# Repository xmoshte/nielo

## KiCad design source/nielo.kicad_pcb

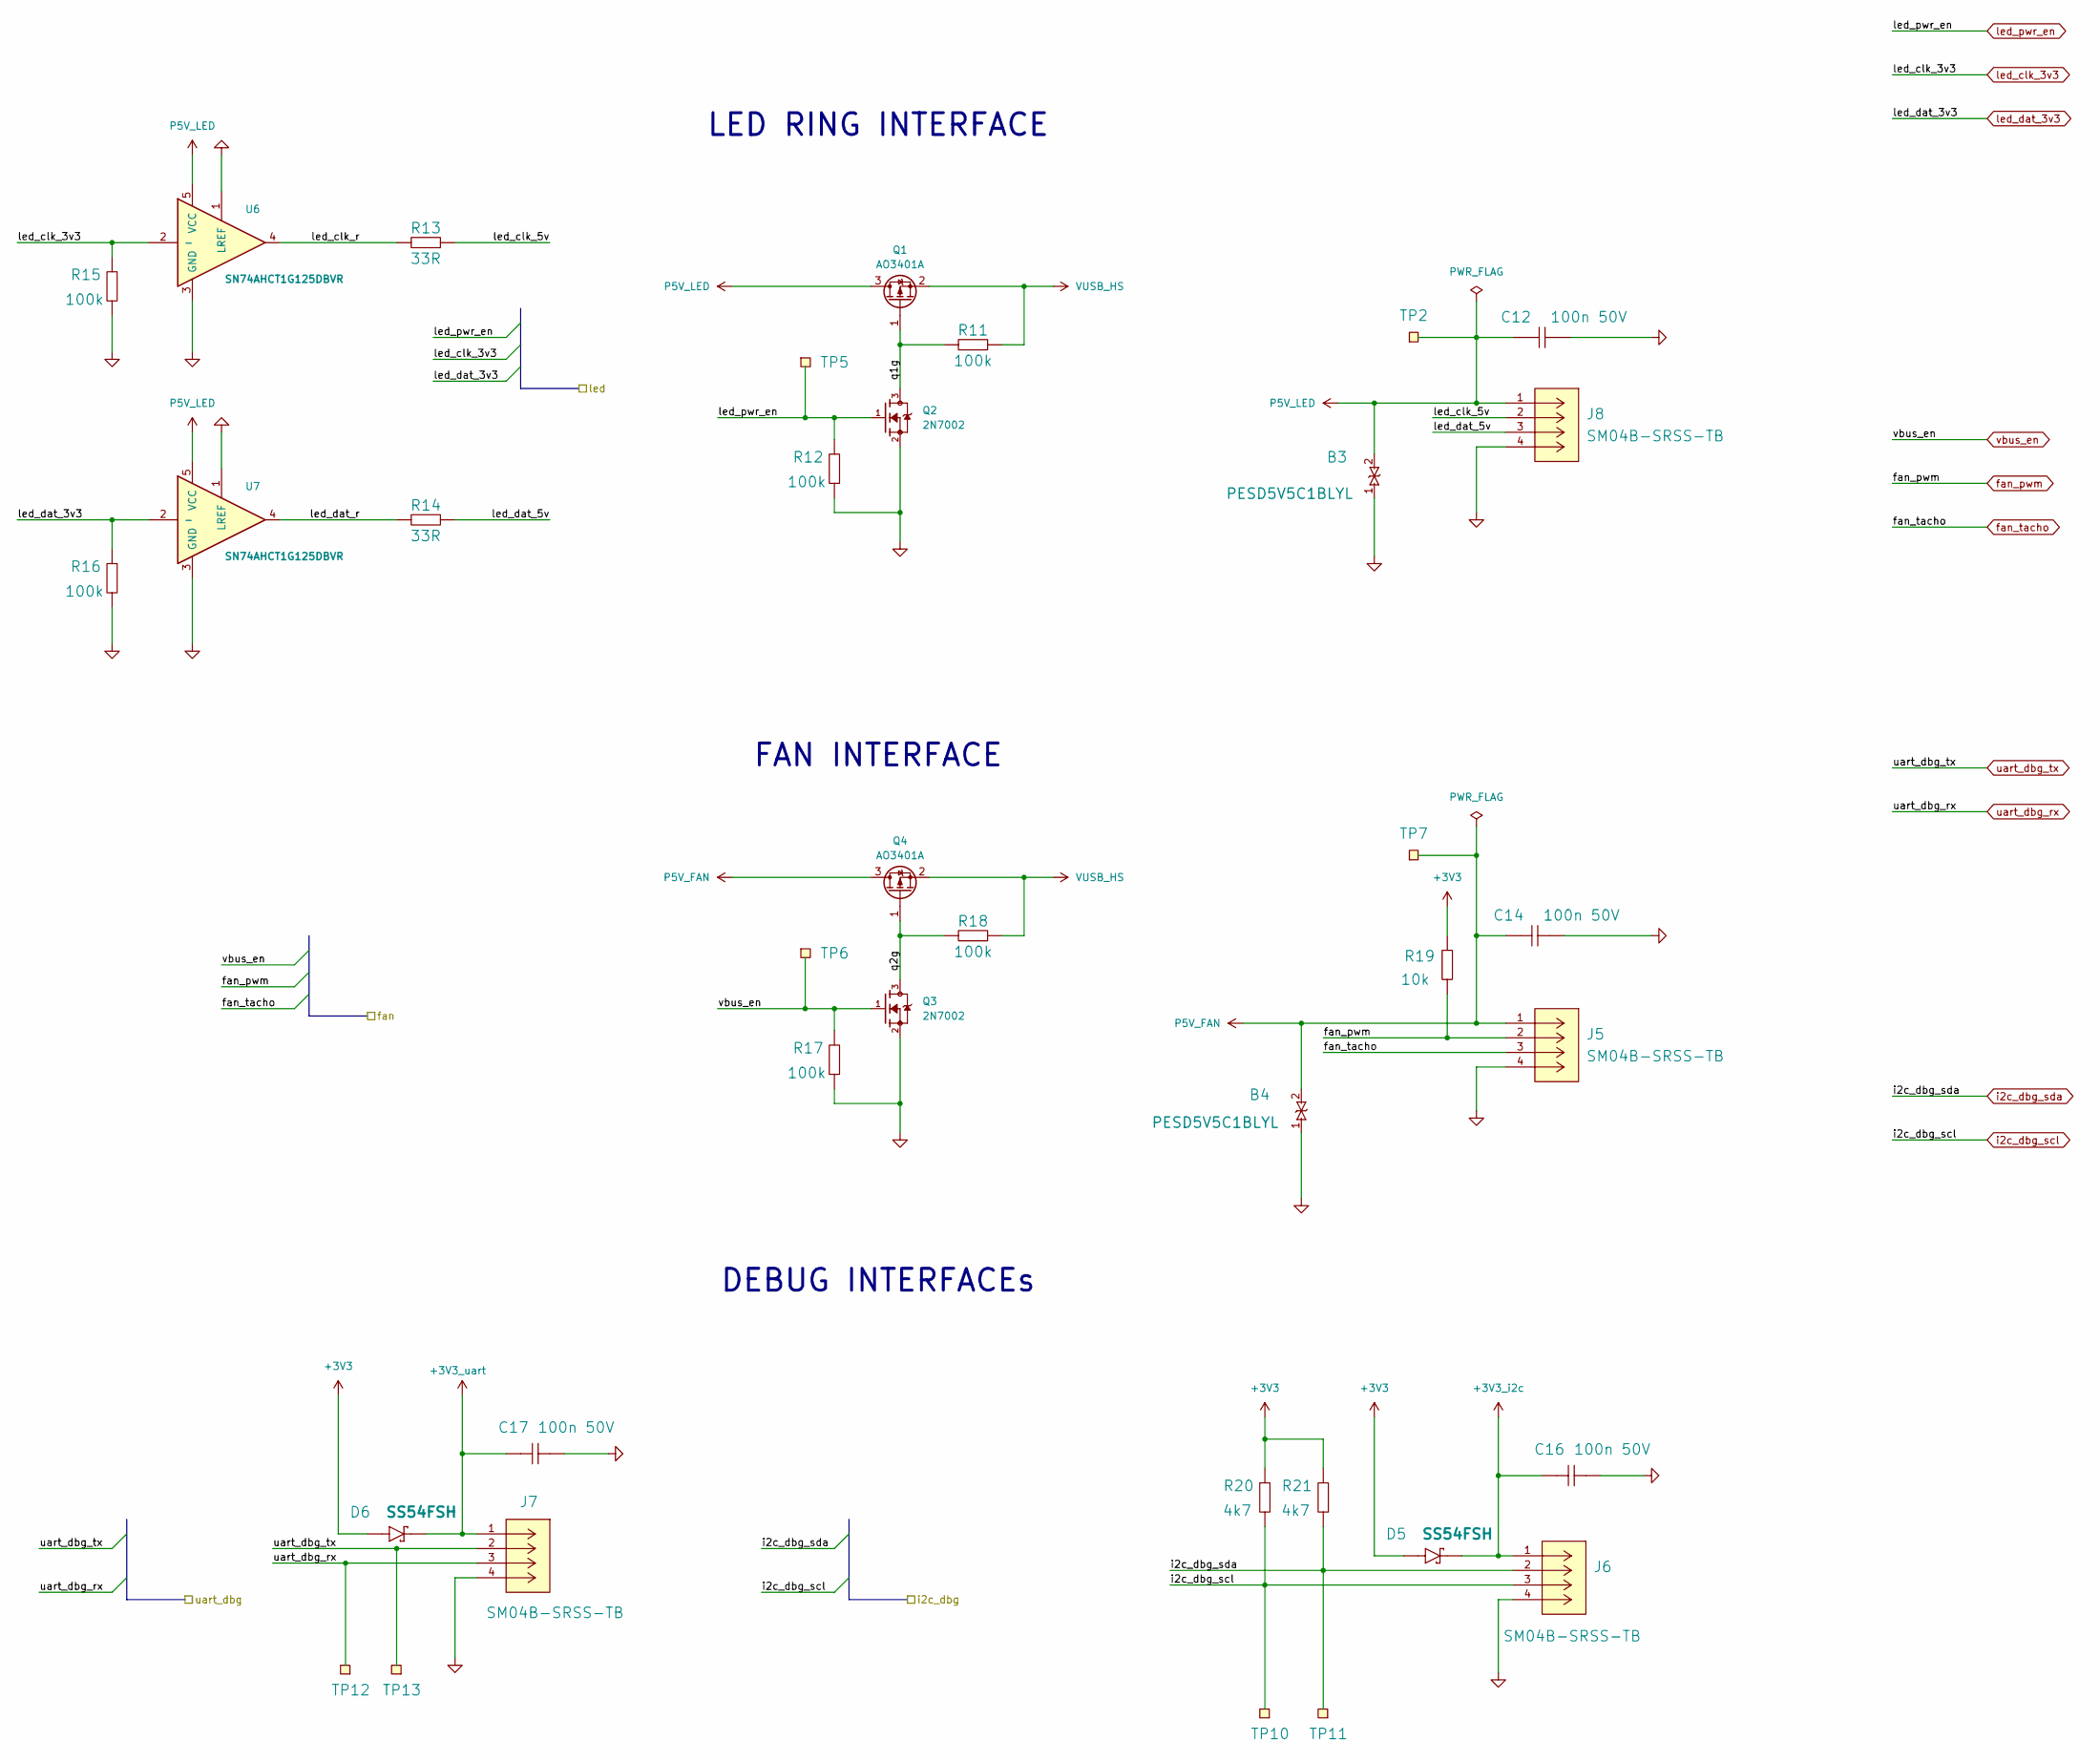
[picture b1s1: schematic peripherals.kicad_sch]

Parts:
B3, B4: PESD5V5C1BLYL; MPN PESD5V5C1BLYL; LCSC No C18212174
C12, C14, C16, C17: 100n 50V; CAPC1005X04L; MPN 04025C104JAT2A; DigiKey No 478-KGM05CR71H104JHTR-ND
D5, D6: SS54FSH; SODFL4725X110N; MPN SS54FSH; LCSC No C19855357
J5, J6, J7, J8: SM04B-SRSS-TB; CONN_SM04B-SRSS-TB_JST; MPN SM04B-SRSS-TB; Mouser No 306-SM04BSRSSTBLFSN
Q1, Q4: AO3401A; SOT-23-3L_AOS; MPN AO3401A; DigiKey No 785-1001-2-ND
Q2, Q3: 2N7002; SOT95P240X111-3N; MPN 2N7002; Mouser No 512-2N7002
R11, R12, R15, R16, R17, R18: 100k; RESC1005X04L; MPN CR0402-JW-104GLF; LCSC No C203104
R13, R14: 33R; RESC1005X04L; MPN MCS0402MC3309FE000; LCSC No C2074234
R19: 10k; RESC1005X04L; MPN MCS0402MD1002BE500; LCSC No C2073498
R20, R21: 4k7; RESC1005X04L; MPN RCA04024K70FKED; LCSC No C1858949
TP2, TP5, TP6, TP7, TP10, TP11, TP12, TP13: TP_SMD_D1.5mm
U6, U7: SN74AHCT1G125DBVR; SOT95P280X145-5N; MPN SN74AHCT1G125DBVR; Mouser No 595-SNAHCT1G125DBVR

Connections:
+3V3: D5.A, D6.A, R19.2, R20.2, R21.2; also elsewhere on the board
+3V3_i2c: C16.2, D5.C (K), J6.1
+3V3_uart: C17.2, D6.C (K), J7.1
/peripherals/led_clk_5v: J8.2, R13.2
/peripherals/led_clk_r: R13.1, U6.4
/peripherals/led_dat_5v: J8.3, R14.2
/peripherals/led_dat_r: R14.1, U7.4
/peripherals/q1g: Q1.1 (G), Q2.3, R11.1
/peripherals/q2g: Q3.3, Q4.1 (G), R18.1
GND: B3.1 (K1), B4.1 (K1), C12.1, C14.1, C16.1, C17.1, J5.4, J6.4, J7.4, J8.4, Q2.2, Q3.2, R12.1, R15.1, R16.1, R17.1, U6.1 (LREF), U6.3 (GND), U7.1 (LREF), U7.3 (GND); also elsewhere on the board
P5V_FAN: B4.2 (K2), C14.2, J5.1, Q4.3 (D), TP7.1 (1_1)
P5V_LED: B3.2 (K2), C12.2, J8.1, Q1.3 (D), TP2.1 (1_1), U6.5 (VCC), U7.5 (VCC)
VUSB_HS: Q1.2 (S), Q4.2 (S), R11.2, R18.2; also elsewhere on the board
fan_pwm: J5.2, R19.1; also elsewhere on the board
fan_tacho: J5.3; also elsewhere on the board
i2c_dbg_scl: J6.3, R20.1, TP10.1 (1_1); also elsewhere on the board
i2c_dbg_sda: J6.2, R21.1, TP11.1 (1_1); also elsewhere on the board
led_clk_3v3: R15.2, U6.2 (-); also elsewhere on the board
led_dat_3v3: R16.2, U7.2 (-); also elsewhere on the board
led_pwr_en: Q2.1, R12.2, TP5.1 (1_1); also elsewhere on the board
uart_dbg_rx: J7.3, TP12.1 (1_1); also elsewhere on the board
uart_dbg_tx: J7.2, TP13.1 (1_1); also elsewhere on the board
vbus_en: Q3.1, R17.2, TP6.1 (1_1); also elsewhere on the board

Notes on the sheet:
LED RING INTERFACE
DEBUG INTERFACEs
FAN INTERFACE

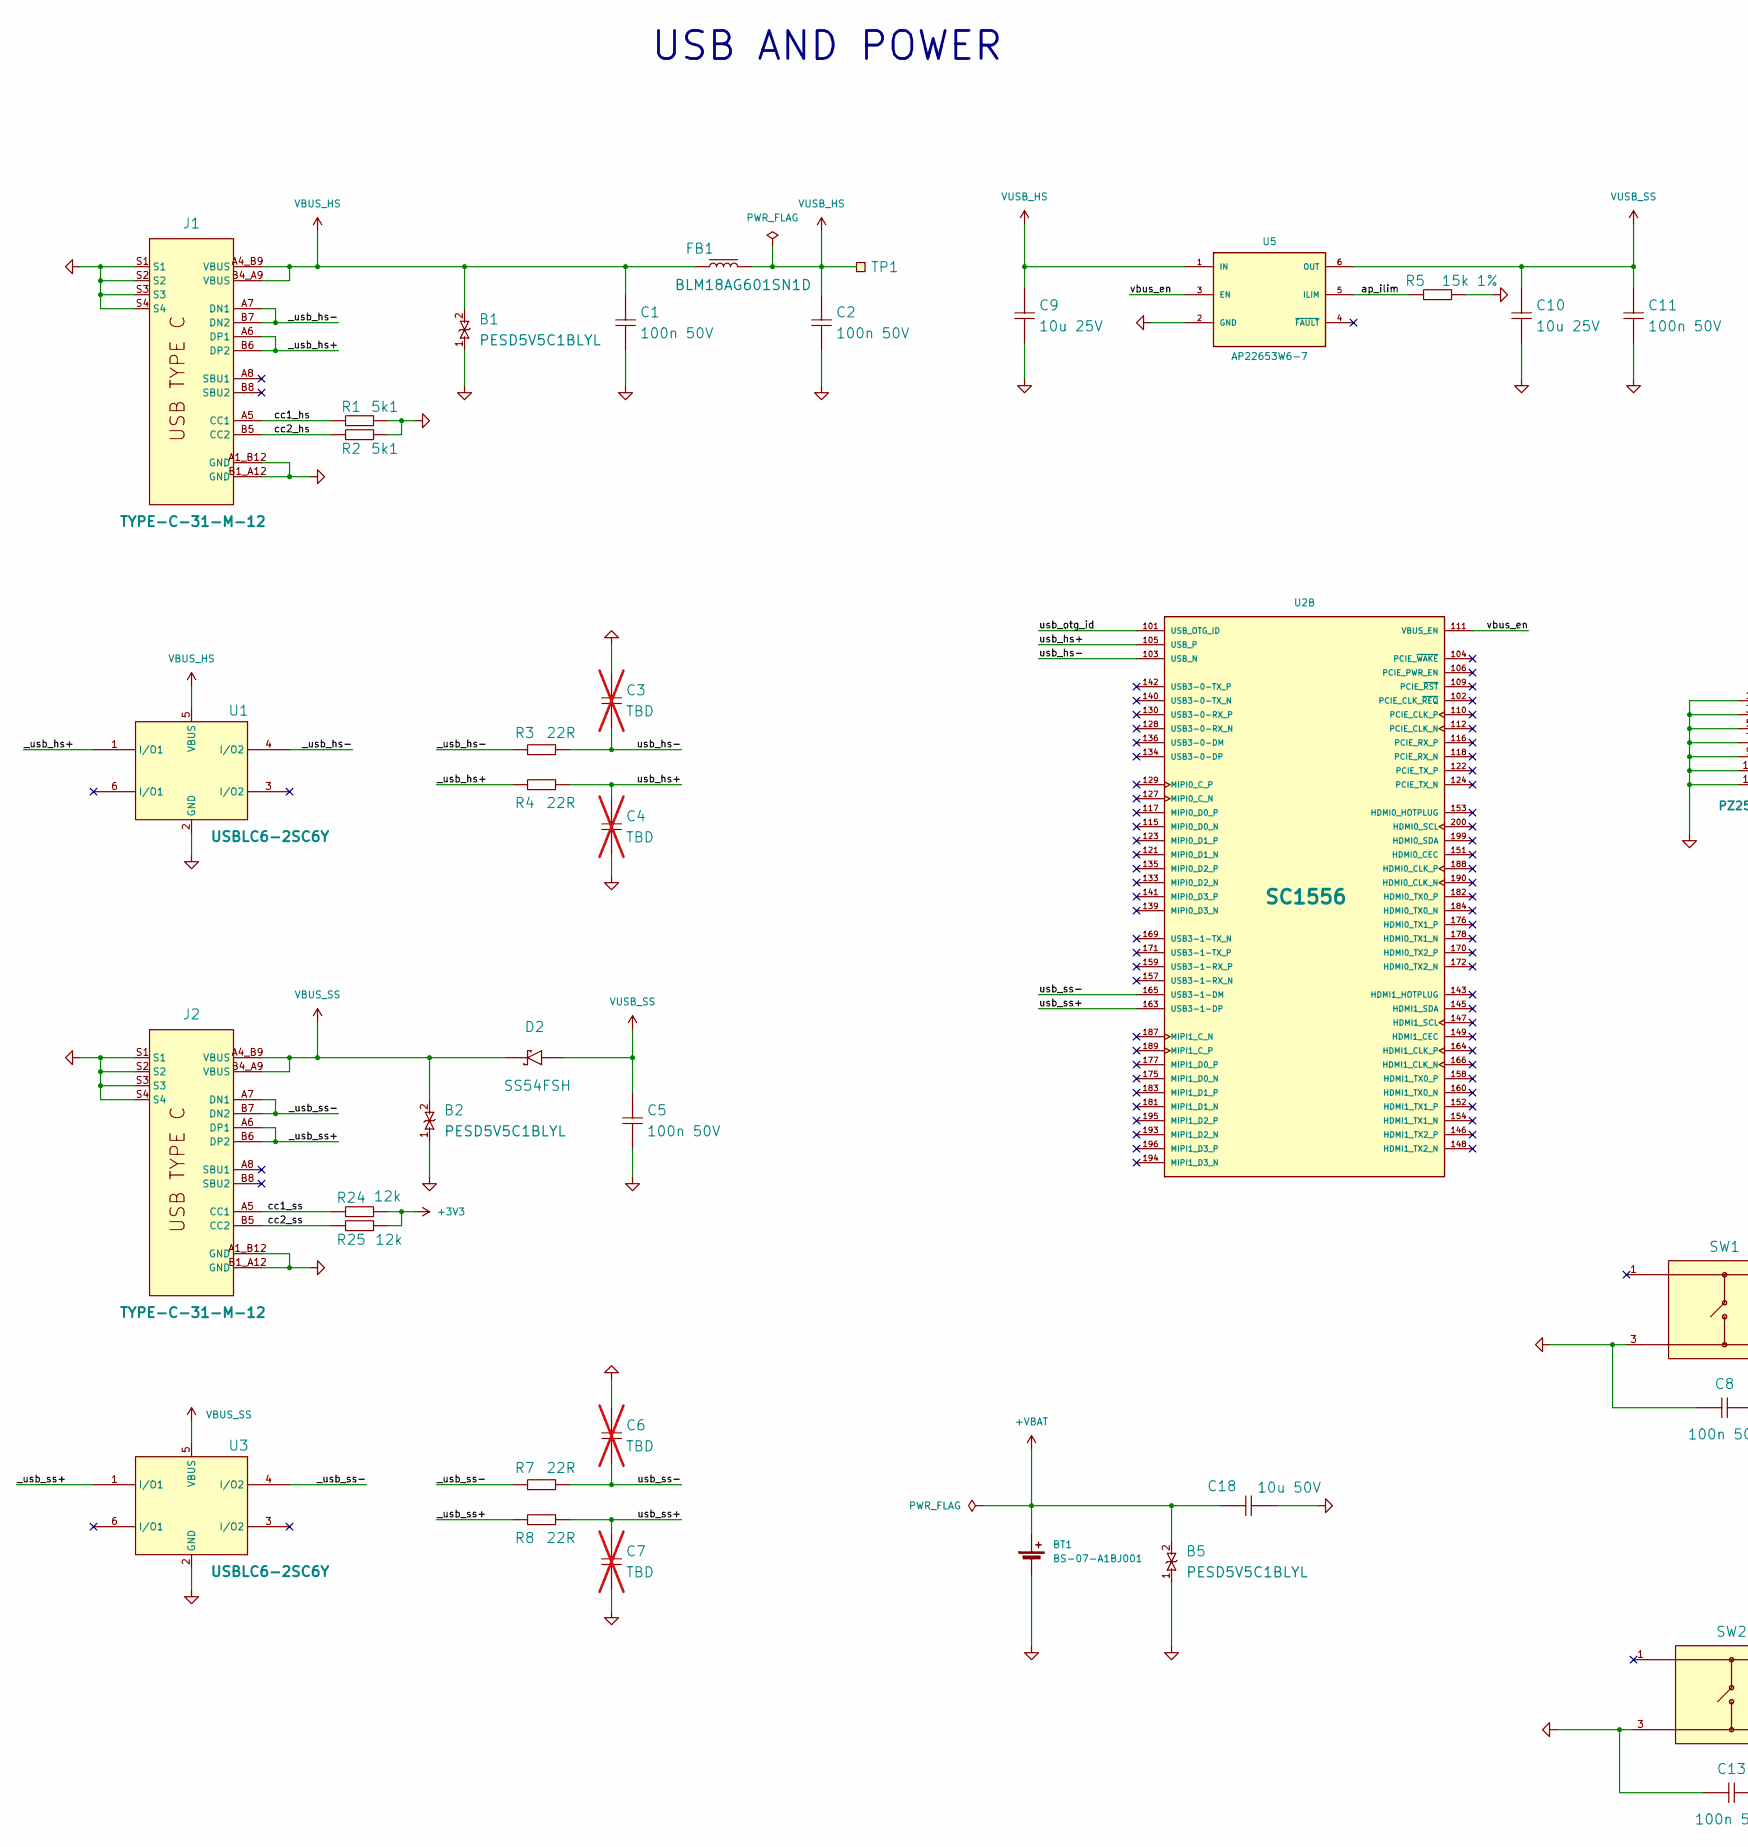
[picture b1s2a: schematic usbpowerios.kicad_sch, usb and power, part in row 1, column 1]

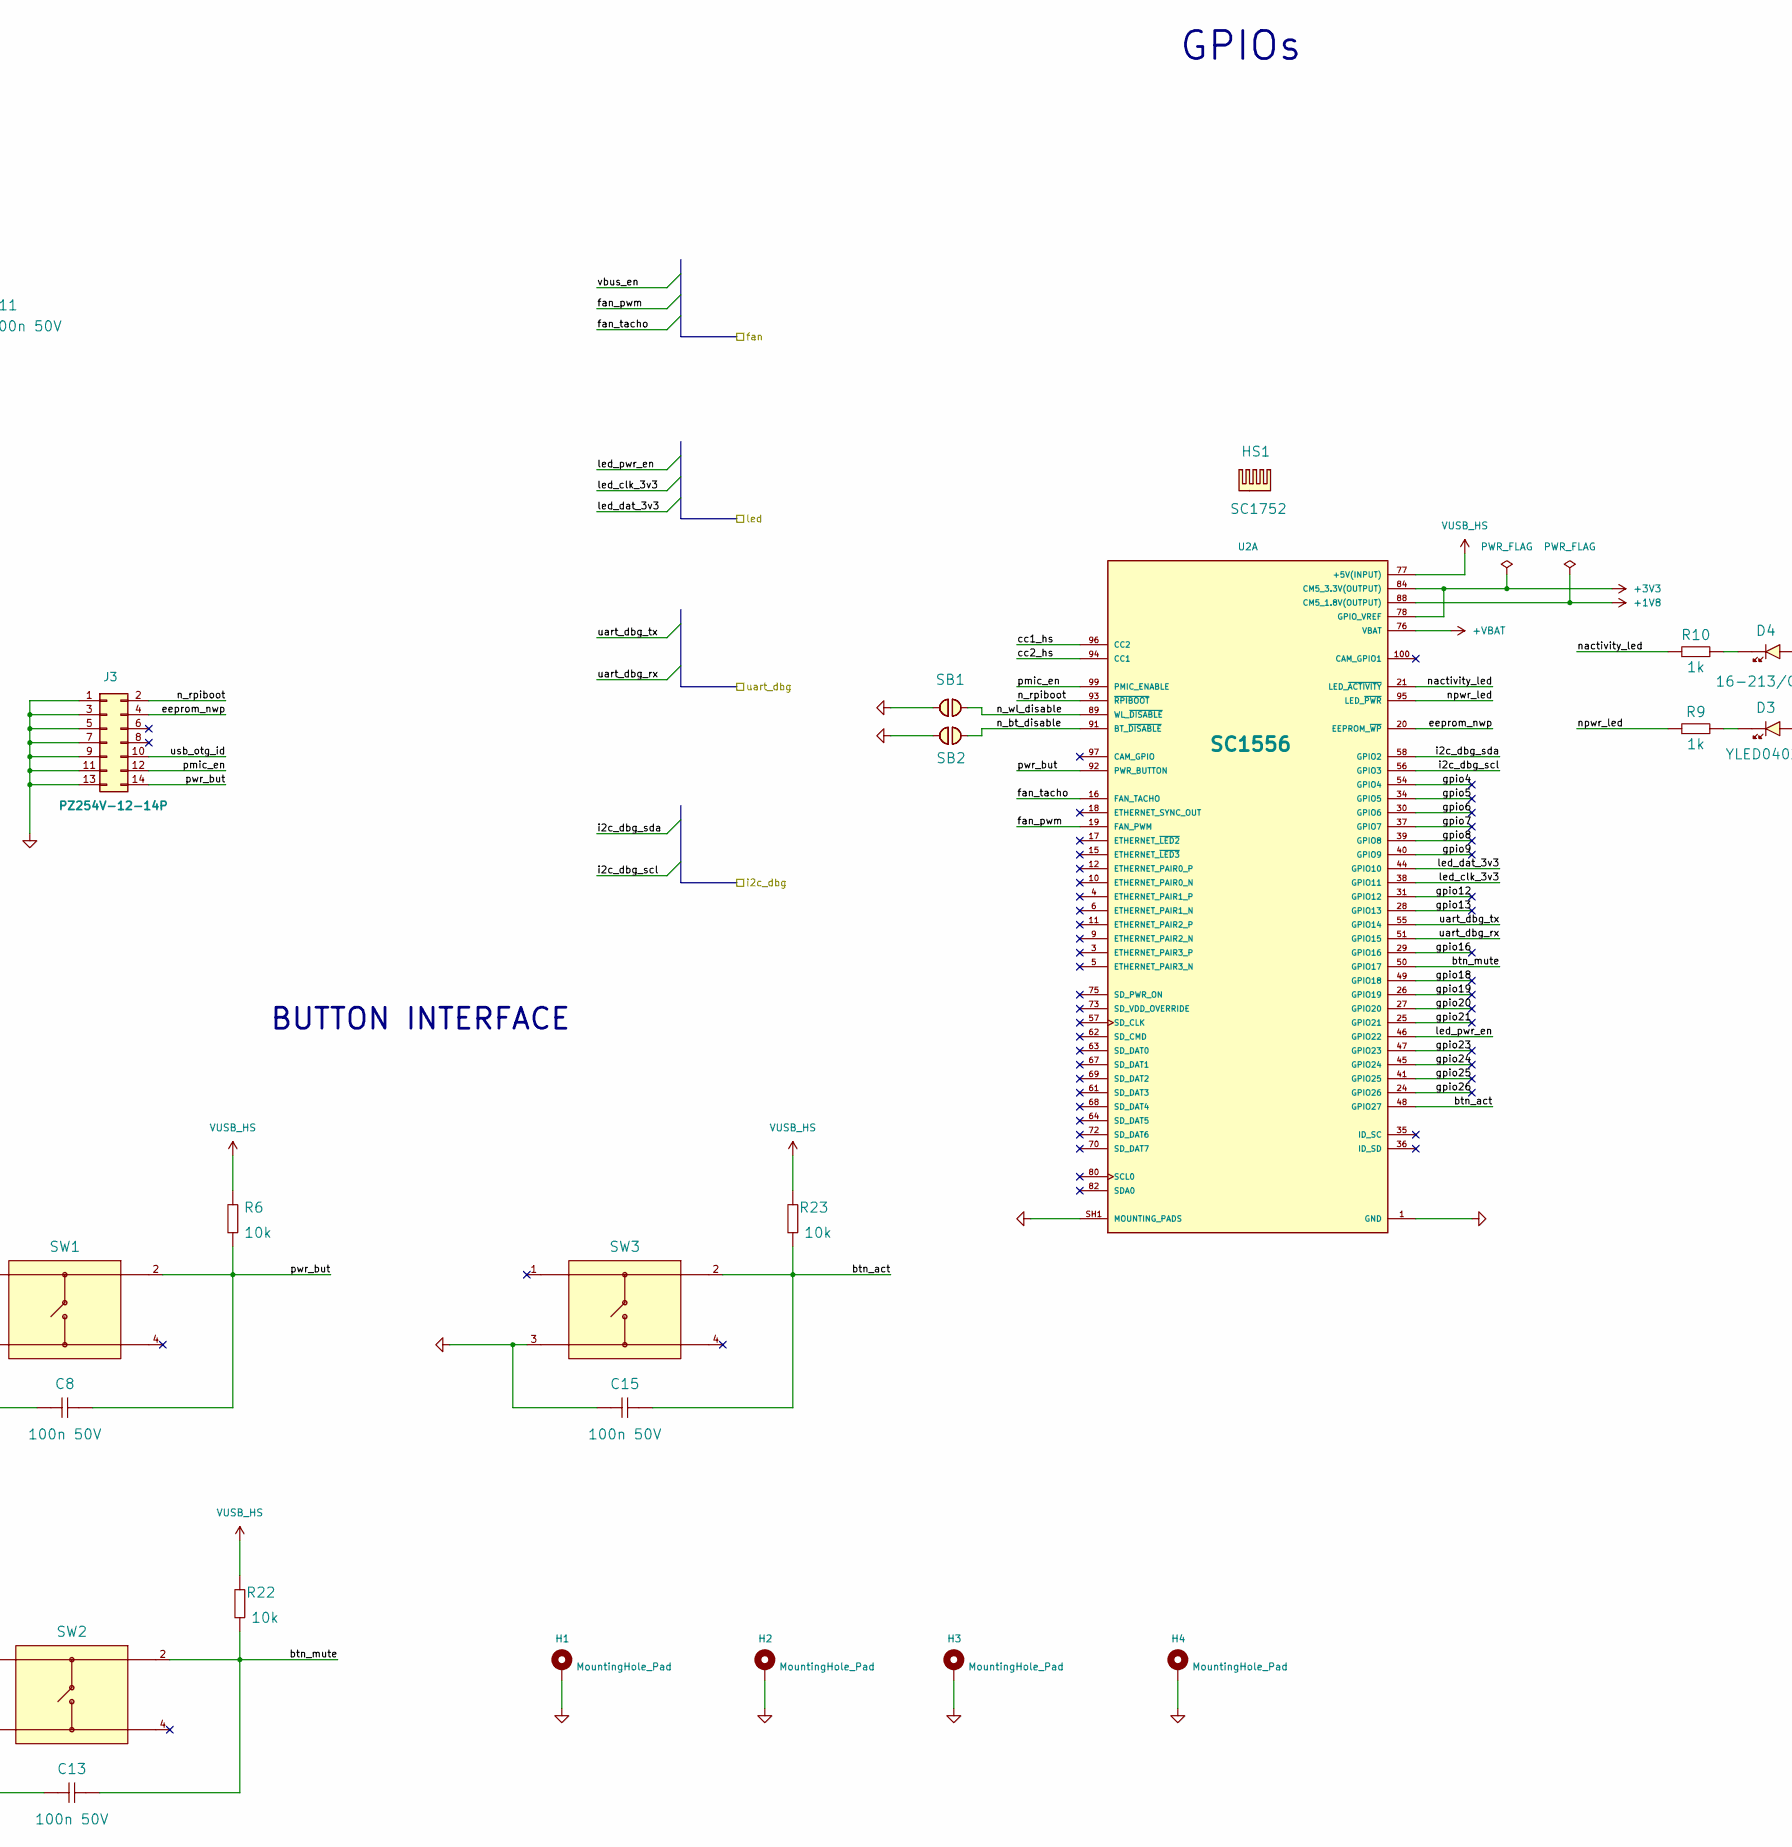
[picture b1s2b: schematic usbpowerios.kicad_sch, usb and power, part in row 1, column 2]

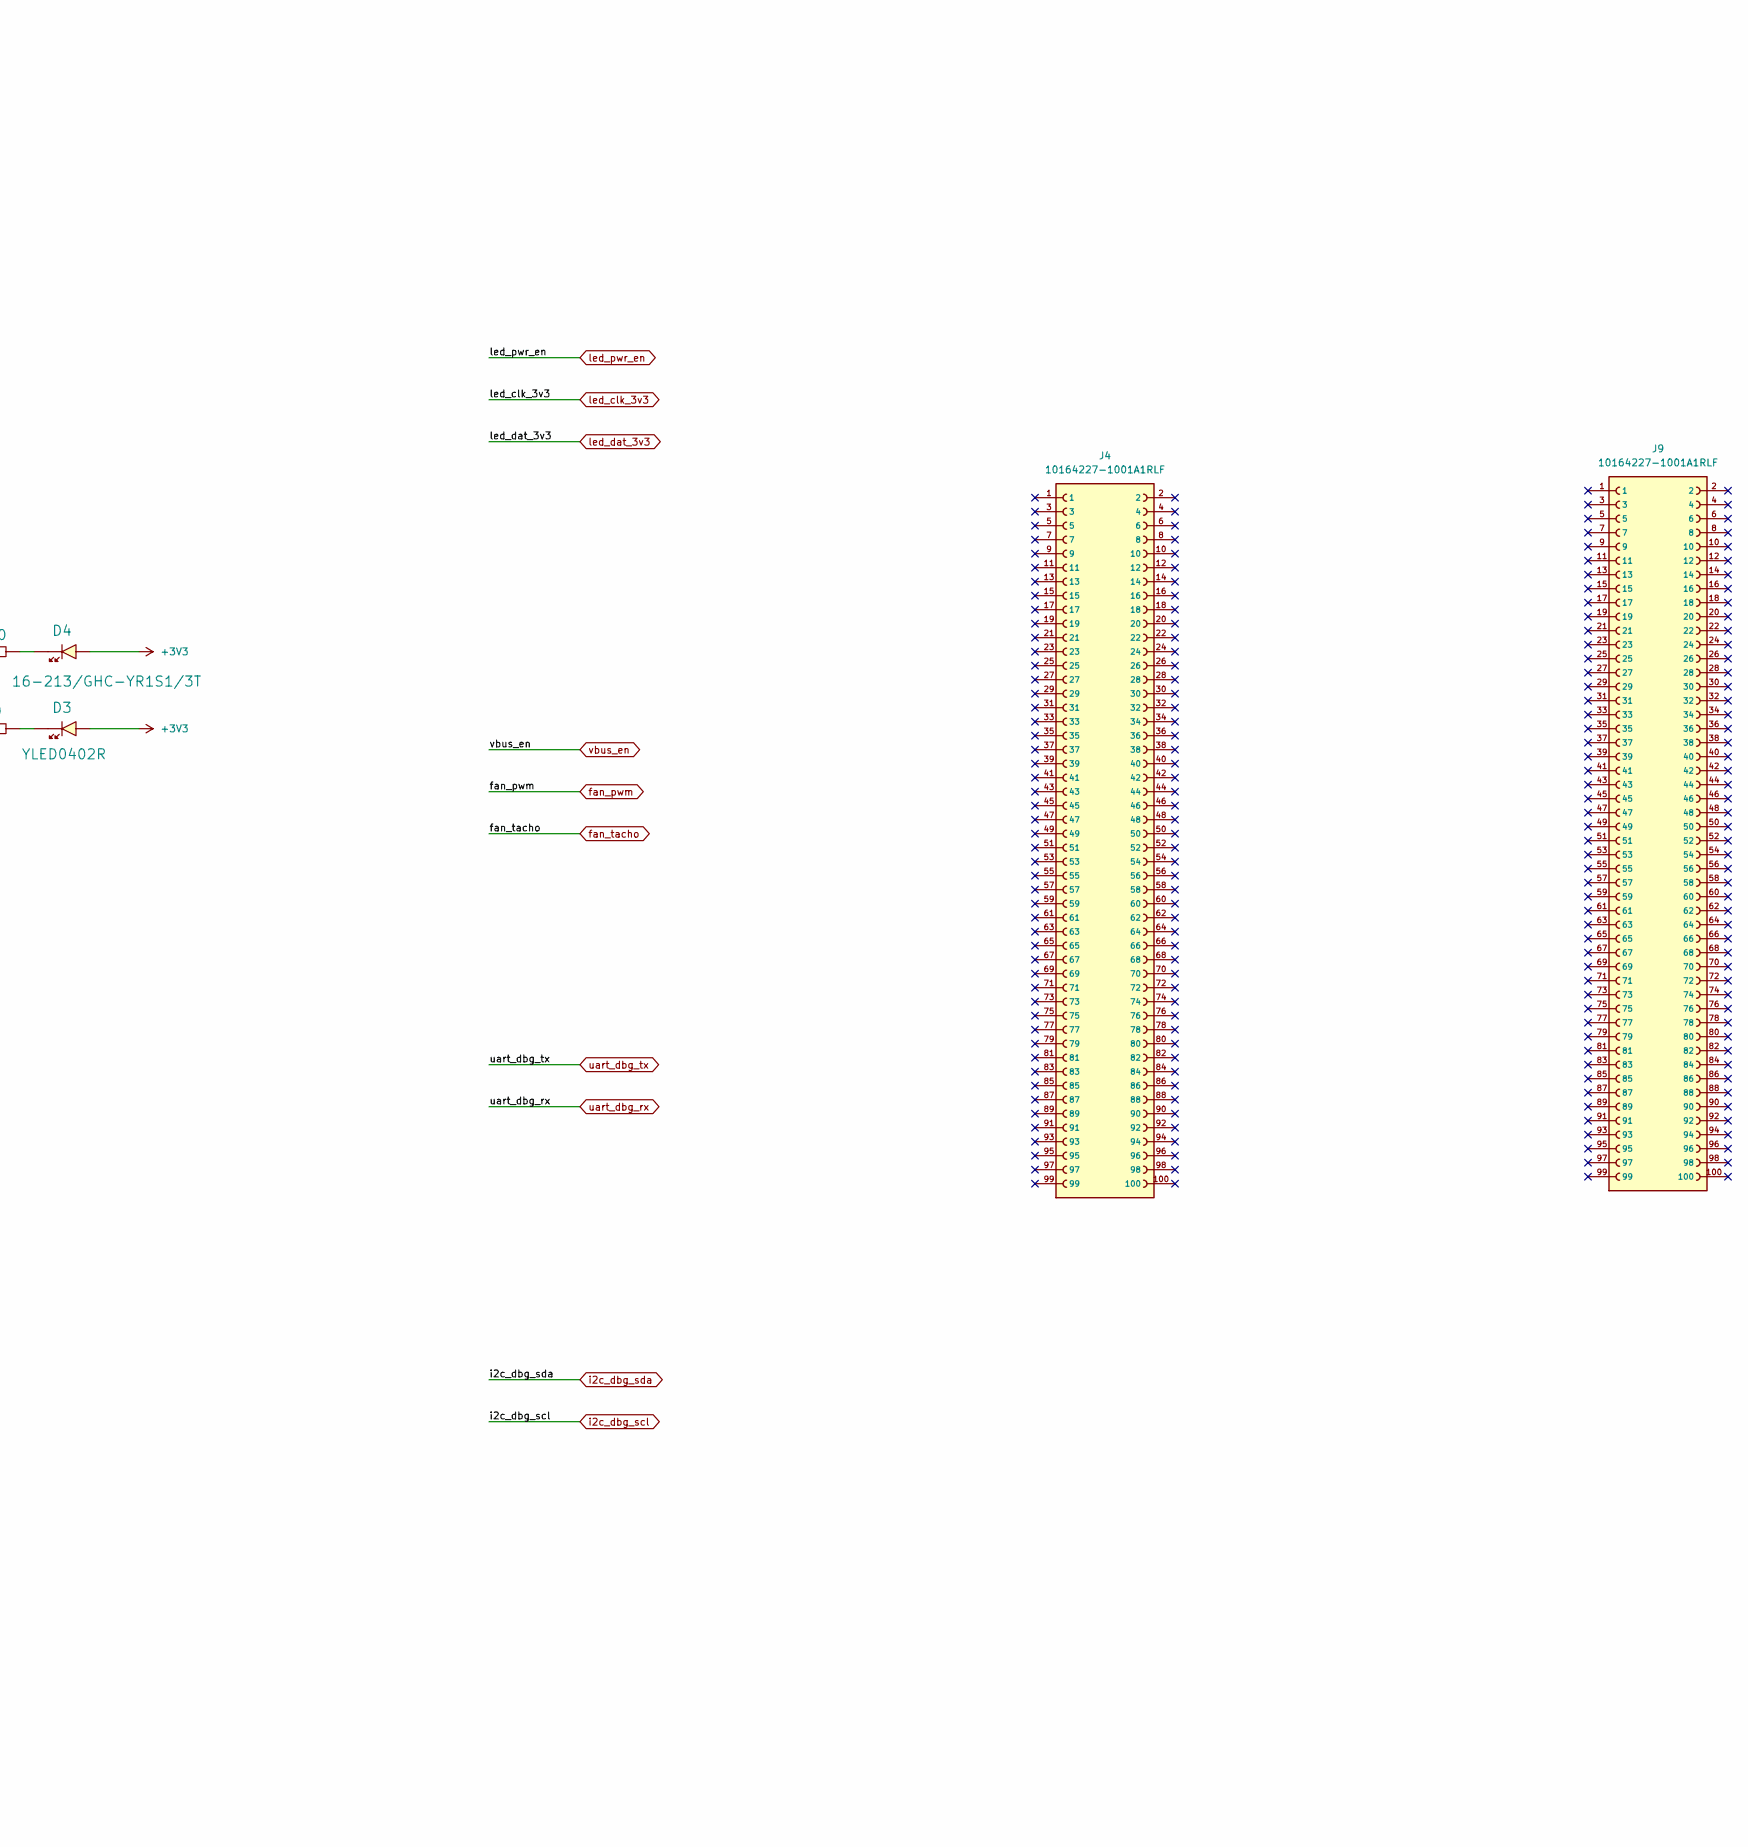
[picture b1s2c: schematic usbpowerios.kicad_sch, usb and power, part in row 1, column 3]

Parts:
B1, B2, B5: PESD5V5C1BLYL; MPN PESD5V5C1BLYL; LCSC No C18212174
BT1: BS-07-A1BJ001; BatteryHolder_MYOUNG_BS-07-A1BJ001_CR2032; MPN BS-07-A1BJ001; LCSC No C2979167
C1, C2, C5, C8, C13, C15: 100n 50V; CAPC1005X04L; MPN 04025C104JAT2A; DigiKey No 478-KGM05CR71H104JHTR-ND
C3, C4, C6, C7: TBD; CAPC1005X04L; MPN TBD; not fitted
C9, C10: 10u 25V; CAPC1608X06L; MPN CC0603KRX5R8BB106; DigiKey No 13-CC0603KRX5R8BB106TR-ND
C11: 100n 50V; CAPC1608X06L; MPN CML0603X7R104KT50V; DigiKey No 738-CML0603X7R104KT50VTR-ND
C18: 10u 50V; CAPC2012X11L; MPN KGM21FS61E106KU; DigiKey No 478-KGM21FS61E106KUTR-ND
D2: SS54FSH; SODFL4725X110N; MPN SS54FSH; LCSC No C19855357
D3: YLED0402R; LED_0402_RED; MPN YLED0402R; LCSC No C21260817
D4: 16-213/GHC-YR1S1/3T; LED_0402_GREEN; MPN 16-213/GHC-YR1S1/3T; LCSC No C74338
FB1: BLM18AG601SN1D; FB_0603; MPN BLM18AG601SN1D; LCSC No C19330
H1, H2, H3, H4: MountingHole_Pad; MountingHole_2.2mm_M2_Pad_Via
HS1: SC1752; MPN SC1752; Mouser No 358-SC1752
J1, J2: TYPE-C-31-M-12; HRO_TYPE-C-31-M-12; MPN TYPE-C-31-M-12; LCSC No C165948
J3: PZ254V-12-14P; MPN PZ254V-12-14P; LCSC No C492424
J4, J9: 10164227-1001A1RLF; MPN 10164227-1001A1RLF; Mouser No 649-01642271001A1RLF
R1, R2: 5k1; RESC1005X04L; MPN TNPW04025K10BEED; LCSC No C2088796
R3, R4, R7, R8: 22R; RESC1005X04L; MPN CR0402-JW-220GLF; LCSC No C2076445
R5: 15k 1%; RESC1005X04L; MPN MCS04020C1502FE500; LCSC No C2074222
R6, R22, R23: 10k; RESC1005X04L; MPN MCS0402MD1002BE500; LCSC No C2073498
R9, R10: 1k; RESC1005X04L; MPN CRCW04021K65FKEE; LCSC No C2076615
R24, R25: 12k; RESC1005X04L; MPN CR0402-FX-1202GLF; LCSC No C2085429
SB1, SB2: solderbridge; Solderbridge
SW1, SW2, SW3: Tactile Switch; PTS815; MPN PTS815SJM250SMTRLFS; LCSC No C2689510
TP1: TP_SMD_D1.5mm
U1, U3: USBLC6-2SC6Y; SOT23-6L_STM; MPN USBLC6-2SC6Y; LCSC No C2969755
U2: SC1556; MODULE_CM5002000; MPN SC1556; Mouser No 358-SC1556
U5: AP22653W6-7; SOT95P280X145-6N; MPN AP22653W6-7; Mouser No 621-AP22653W6-7

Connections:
+1V8: U2.88 (CM5_1.8V(OUTPUT)), U2.90 (CM5_1.8V(OUTPUT))
+3V3: D3.A, D4.A, R24.2, R25.2, U2.78 (GPIO_VREF), U2.84 (CM5_3.3V(OUTPUT)), U2.86 (CM5_3.3V(OUTPUT)); also elsewhere on the board
+VBAT: B5.2 (K2), BT1.1 (+), C18.1, U2.76 (VBAT)
/usbpowerios/_usb_hs+: J1.A6 (DP1), J1.B6 (DP2), R4.1, U1.1 (I/O1)
/usbpowerios/_usb_hs-: J1.A7 (DN1), J1.B7 (DN2), R3.1, U1.4 (I/O2)
/usbpowerios/_usb_ss+: J2.A6 (DP1), J2.B6 (DP2), R8.1, U3.1 (I/O1)
/usbpowerios/_usb_ss-: J2.A7 (DN1), J2.B7 (DN2), R7.1, U3.4 (I/O2)
/usbpowerios/ap_ilim: R5.1, U5.5 (ILIM)
/usbpowerios/btn_act: C15.1, R23.1, SW3.2, U2.48 (GPIO27)
/usbpowerios/btn_mute: C13.1, R22.1, SW2.2, U2.50 (GPIO17)
/usbpowerios/cc1_hs: J1.A5 (CC1), R1.1, U2.96 (CC2)
/usbpowerios/cc1_ss: J2.A5 (CC1), R24.1
/usbpowerios/cc2_hs: J1.B5 (CC2), R2.1, U2.94 (CC1)
/usbpowerios/cc2_ss: J2.B5 (CC2), R25.1
/usbpowerios/eeprom_nwp: J3.4, U2.20 (EEPROM_~WP)
/usbpowerios/gpio4: U2.54 (GPIO4)
/usbpowerios/gpio5: U2.34 (GPIO5)
/usbpowerios/gpio6: U2.30 (GPIO6)
/usbpowerios/gpio7: U2.37 (GPIO7)
/usbpowerios/gpio8: U2.39 (GPIO8)
/usbpowerios/gpio9: U2.40 (GPIO9)
/usbpowerios/gpio12: U2.31 (GPIO12)
/usbpowerios/gpio13: U2.28 (GPIO13)
/usbpowerios/gpio16: U2.29 (GPIO16)
/usbpowerios/gpio18: U2.49 (GPIO18)
/usbpowerios/gpio19: U2.26 (GPIO19)
/usbpowerios/gpio20: U2.27 (GPIO20)
/usbpowerios/gpio21: U2.25 (GPIO21)
/usbpowerios/gpio23: U2.47 (GPIO23)
/usbpowerios/gpio24: U2.45 (GPIO24)
/usbpowerios/gpio25: U2.41 (GPIO25)
/usbpowerios/gpio26: U2.24 (GPIO26)
/usbpowerios/n_bt_disable: SB2.1 (0), U2.91 (BT_~DISABLE)
/usbpowerios/n_rpiboot: J3.2, U2.93 (~RPIBOOT)
/usbpowerios/n_wl_disable: SB1.1 (0), U2.89 (WL_~DISABLE)
/usbpowerios/nactivity_led: R10.2, U2.21 (LED_~ACTIVITY)
/usbpowerios/npwr_led: R9.2, U2.95 (LED_~PWR)
/usbpowerios/pmic_en: J3.12, U2.99 (PMIC_ENABLE)
/usbpowerios/pwr_but: C8.1, J3.14, R6.1, SW1.2, U2.92 (PWR_BUTTON)
/usbpowerios/usb_hs+: C4.2, R4.2, U2.105 (USB_P)
/usbpowerios/usb_hs-: C3.1, R3.2, U2.103 (USB_N)
/usbpowerios/usb_otg_id: J3.10, U2.101 (USB_OTG_ID)
/usbpowerios/usb_ss+: C7.2, R8.2, U2.163 (USB3-1-DP)
/usbpowerios/usb_ss-: C6.1, R7.2, U2.165 (USB3-1-DM)
GND: B1.1 (K1), B2.1 (K1), B5.1 (K1), BT1.2 (-), C1.1, C2.1, C3.2, C4.1, C5.1, C6.2, C7.1, C8.2, C9.1, C10.1, C11.1, C13.2, C15.2, C18.2, H1.1 (1_1), H2.1 (1_1), H3.1 (1_1), H4.1 (1_1), J1.A1_B12 (GND), J1.B1_A12 (GND), J1.S1, J1.S2, J1.S3, J1.S4, J2.A1_B12 (GND), J2.B1_A12 (GND), J2.S1, J2.S2, J2.S3, J2.S4, J3.1, J3.3, J3.5, J3.7, J3.9, J3.11, J3.13, R1.2, R2.2, R5.2, SB1.2 (1), SB2.2 (1), SW1.3, SW2.3, SW3.3, U1.2 (GND), U2.1 (GND), U2.2 (GND), U2.7 (GND), U2.8 (GND), U2.13 (GND), U2.14 (GND), U2.22 (GND), U2.23 (GND), U2.32 (GND), U2.33 (GND), U2.42 (GND), U2.43 (GND), U2.52 (GND), U2.53 (GND), U2.59 (GND), U2.60 (GND), U2.65 (GND), U2.66 (GND), U2.71 (GND), U2.74 (GND), U2.98 (GND), U2.107 (GND), U2.108 (GND), U2.113 (GND), U2.114 (GND), U2.119 (GND), U2.120 (GND), U2.125 (GND), U2.126 (GND), U2.131 (GND), U2.132 (GND), U2.137 (GND), U2.138 (GND), U2.144 (GND), U2.150 (GND), U2.155 (GND), U2.156 (GND), U2.161 (GND), U2.162 (GND), U2.167 (GND), U2.168 (GND), U2.173 (GND), U2.174 (GND), U2.179 (GND), U2.180 (GND), U2.185 (GND), U2.186 (GND), U2.191 (GND), U2.192 (GND), U2.197 (GND), U2.198 (GND), U2.SH1 (MOUNTING_PADS), U2.SH2 (MOUNTING_PADS), U2.SH3 (MOUNTING_PADS), U2.SH4 (MOUNTING_PADS), U3.2 (GND), U5.2 (GND); also elsewhere on the board
unnamed: D3.K, R9.1
unnamed: D4.K, R10.1
VBUS_HS: B1.2 (K2), C1.2, FB1.1, J1.A4_B9 (VBUS), J1.B4_A9 (VBUS), U1.5 (VBUS)
VBUS_SS: B2.2 (K2), D2.C (K), J2.A4_B9 (VBUS), J2.B4_A9 (VBUS), U3.5 (VBUS)
VUSB_HS: C2.2, C9.2, FB1.2, R6.2, R22.2, R23.2, TP1.1 (1_1), U2.77 (+5V(INPUT)), U2.79 (+5V(INPUT)), U2.81 (+5V(INPUT)), U2.83 (+5V(INPUT)), U2.85 (+5V(INPUT)), U2.87 (+5V(INPUT)), U5.1 (IN); also elsewhere on the board
VUSB_SS: C5.2, C10.2, C11.2, D2.A, U5.6 (OUT)
fan_pwm: U2.19 (FAN_PWM); also elsewhere on the board
fan_tacho: U2.16 (FAN_TACHO); also elsewhere on the board
i2c_dbg_scl: U2.56 (GPIO3); also elsewhere on the board
i2c_dbg_sda: U2.58 (GPIO2); also elsewhere on the board
led_clk_3v3: U2.38 (GPIO11); also elsewhere on the board
led_dat_3v3: U2.44 (GPIO10); also elsewhere on the board
led_pwr_en: U2.46 (GPIO22); also elsewhere on the board
uart_dbg_rx: U2.51 (GPIO15); also elsewhere on the board
uart_dbg_tx: U2.55 (GPIO14); also elsewhere on the board
vbus_en: U2.111 (VBUS_EN), U5.3 (EN); also elsewhere on the board

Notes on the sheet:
GPIOs
BUTTON INTERFACE
USB AND POWER
